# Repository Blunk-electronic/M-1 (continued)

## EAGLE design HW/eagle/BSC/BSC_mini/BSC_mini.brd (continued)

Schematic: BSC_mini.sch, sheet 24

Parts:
D2401, D2402, D2403: 1N4148; S_SOD123
LED2401: blue; S_0805; PART_CODE_BEL LED_PAC_S_0805_VAL_blue
LED2402, LED2404: green; S_0805; PART_CODE_BEL LED_PAC_S_0805_VAL_green
LED2403: yellow; S_0805; PART_CODE_BEL LED_PAC_S_0805_VAL_yellow
R2401, R2402, R2403, R2405, R2407: 2k7; S_0805; PART_CODE_BEL R_PAC_S_0805_VAL_2k7
R2404: 330; S_0805; PART_CODE_BEL R_PAC_S_0805_VAL_330
R2406, R2409: 160; S_0805; PART_CODE_BEL R_PAC_S_0805_VAL_160
R2408: 470; S_0805; PART_CODE_BEL R_PAC_S_0805_VAL_470
T2401, T2402, T2403, T2404, T2405, T2406: NX2301P; S_SOT23; PART_CODE_BEL T_PAC_S_SOT23_VAL_NX2301P
T2407, T2408: DMG3420U; S_SOT23; PART_CODE_BEL T_PAC_S_SOT23_VAL_DMG3420U

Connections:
GND: LED2401.C, LED2402.C, LED2404.C, R2401.2, R2402.2, R2403.2, R2405.2, T2407.2 (S), T2408.2 (S); also elsewhere on the board
MON_SP_1_VCC_P1V5_LED_A: LED2401.A, R2404.1
MON_SP_1_VCC_P1V8_LED_A: LED2402.A, R2406.2
MON_SP_1_VCC_P2V5_LED_A: LED2404.A, R2409.2
MON_SP_1_VCC_P3V3_D: R2407.2, T2407.3 (D), T2408.1 (G)
MON_SP_1_VCC_P3V3_G: D2401.C, D2402.C, D2403.C, R2405.1, T2407.1 (G)
MON_SP_1_VCC_P3V3_LED_A: LED2403.A, R2408.2
MON_SP_1_VCC_P3V3_LED_C: LED2403.C, T2408.3 (D)
P3V3: R2407.1, R2408.1, T2401.2 (S), T2402.2 (S), T2403.2 (S), T2404.2 (S), T2405.2 (S), T2406.2 (S); also elsewhere on the board
SP_1_VCC_P1V5_SET: T2401.1 (G); also elsewhere on the board
SP_1_VCC_P1V5_SET_N: R2401.1, T2401.3 (D), T2404.1 (G)
SP_1_VCC_P1V5_SET_OR: D2403.A, R2404.2, T2404.3 (D)
SP_1_VCC_P1V8_SET: T2402.1 (G); also elsewhere on the board
SP_1_VCC_P1V8_SET_N: R2402.1, T2402.3 (D), T2405.1 (G)
SP_1_VCC_P1V8_SET_OR: D2402.A, R2406.1, T2405.3 (D)
SP_1_VCC_P2V5_SET: T2403.1 (G); also elsewhere on the board
SP_1_VCC_P2V5_SET_N: R2403.1, T2403.3 (D), T2406.1 (G)
SP_1_VCC_P2V5_SET_OR: D2401.A, R2409.1, T2406.3 (D)

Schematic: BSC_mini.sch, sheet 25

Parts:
D2501, D2502, D2503: 1N4148; S_SOD123
LED2501: blue; S_0805; PART_CODE_BEL LED_PAC_S_0805_VAL_blue
LED2502, LED2503: green; S_0805; PART_CODE_BEL LED_PAC_S_0805_VAL_green
LED2504: yellow; S_0805; PART_CODE_BEL LED_PAC_S_0805_VAL_yellow
R2501, R2502, R2503, R2505, R2507: 2k7; S_0805; PART_CODE_BEL R_PAC_S_0805_VAL_2k7
R2504: 330; S_0805; PART_CODE_BEL R_PAC_S_0805_VAL_330
R2506, R2508: 160; S_0805; PART_CODE_BEL R_PAC_S_0805_VAL_160
R2509: 470; S_0805; PART_CODE_BEL R_PAC_S_0805_VAL_470
T2501, T2502, T2503, T2504, T2505, T2506: NX2301P; S_SOT23; PART_CODE_BEL T_PAC_S_SOT23_VAL_NX2301P
T2507, T2508: DMG3420U; S_SOT23; PART_CODE_BEL T_PAC_S_SOT23_VAL_DMG3420U

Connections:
GND: LED2501.C, LED2502.C, LED2503.C, R2501.2, R2502.2, R2503.2, R2505.2, T2507.2 (S), T2508.2 (S); also elsewhere on the board
MON_SP_2_VCC_P1V5_LED_A: LED2501.A, R2504.1
MON_SP_2_VCC_P1V8_LED_A: LED2502.A, R2506.2
MON_SP_2_VCC_P2V5_LED_A: LED2503.A, R2508.2
MON_SP_2_VCC_P3V3_D: R2507.2, T2507.3 (D), T2508.1 (G)
MON_SP_2_VCC_P3V3_G: D2501.C, D2502.C, D2503.C, R2505.1, T2507.1 (G)
MON_SP_2_VCC_P3V3_LED_A: LED2504.A, R2509.2
MON_SP_2_VCC_P3V3_LED_C: LED2504.C, T2508.3 (D)
P3V3: R2507.1, R2509.1, T2501.2 (S), T2502.2 (S), T2503.2 (S), T2504.2 (S), T2505.2 (S), T2506.2 (S); also elsewhere on the board
SP_2_VCC_P1V5_SET: T2501.1 (G); also elsewhere on the board
SP_2_VCC_P1V5_SET_N: R2501.1, T2501.3 (D), T2504.1 (G)
SP_2_VCC_P1V5_SET_OR: D2503.A, R2504.2, T2504.3 (D)
SP_2_VCC_P1V8_SET: T2502.1 (G); also elsewhere on the board
SP_2_VCC_P1V8_SET_N: R2502.1, T2502.3 (D), T2505.1 (G)
SP_2_VCC_P1V8_SET_OR: D2502.A, R2506.1, T2505.3 (D)
SP_2_VCC_P2V5_SET: T2503.1 (G); also elsewhere on the board
SP_2_VCC_P2V5_SET_N: R2503.1, T2503.3 (D), T2506.1 (G)
SP_2_VCC_P2V5_SET_OR: D2501.A, R2508.1, T2506.3 (D)

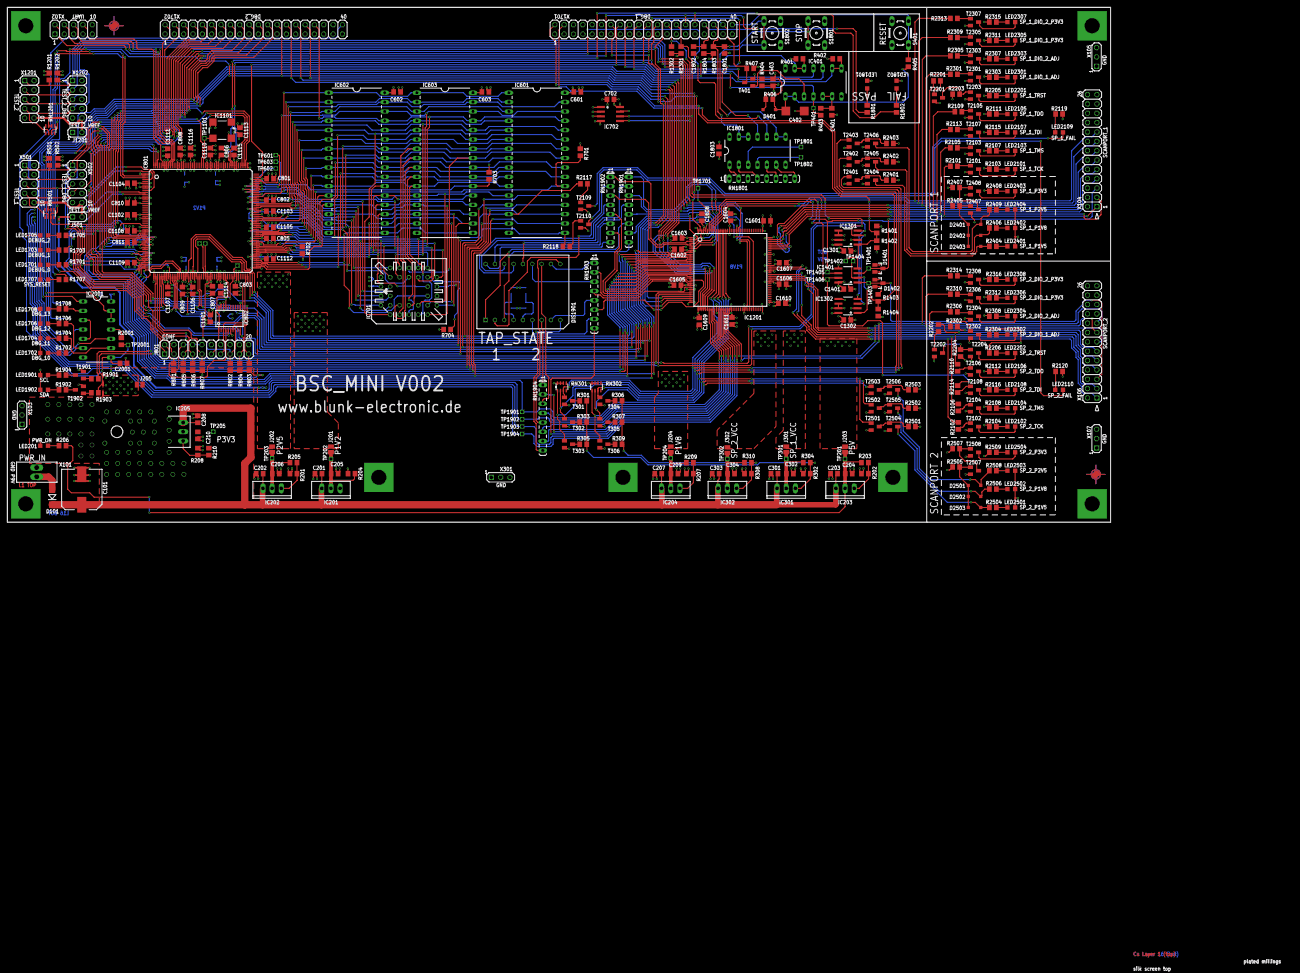
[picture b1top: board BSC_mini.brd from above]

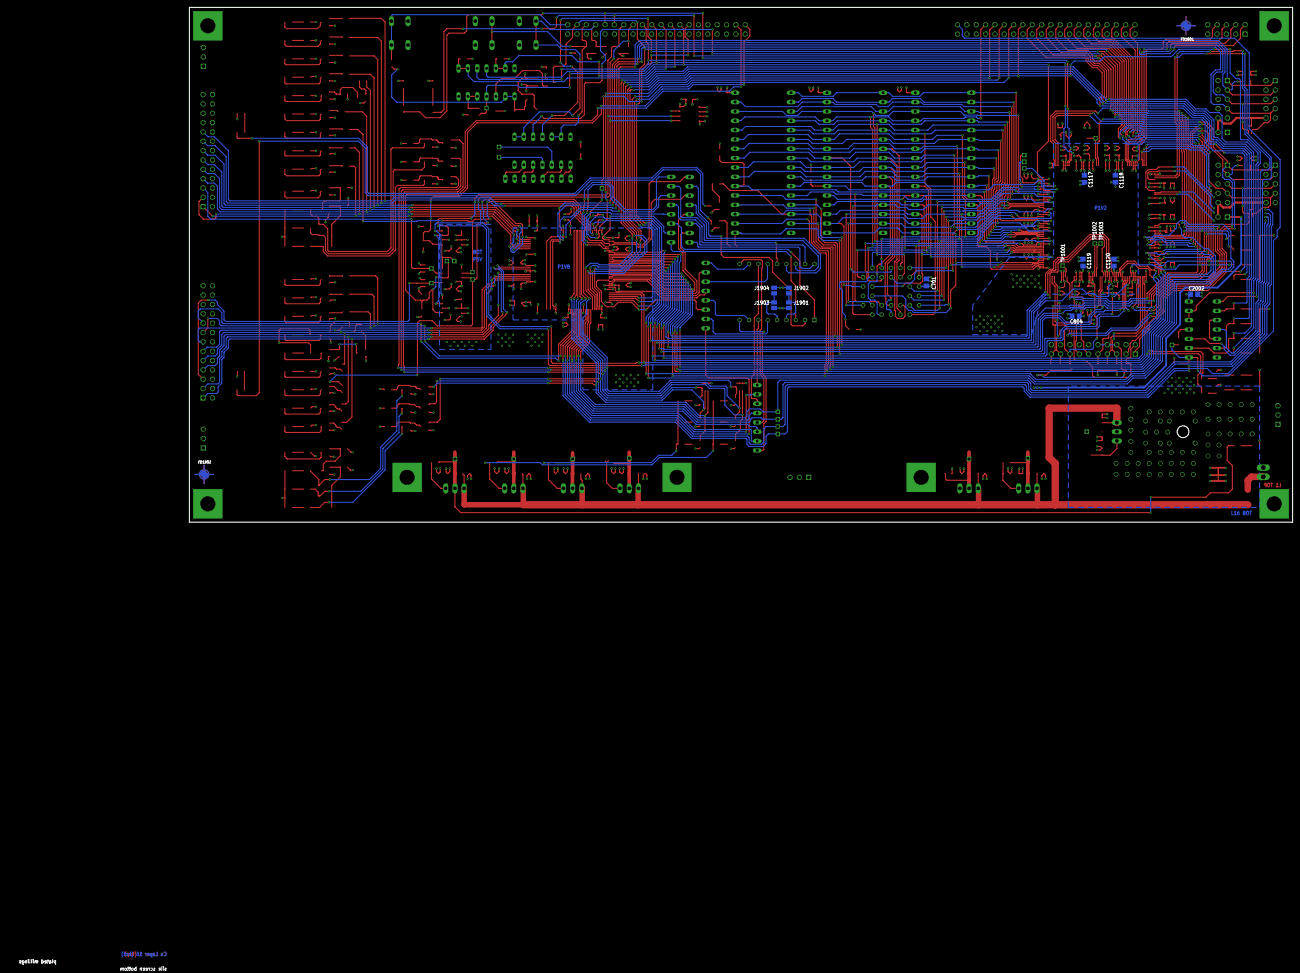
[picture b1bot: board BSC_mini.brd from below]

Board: 4 copper layers, 349.5 x 260.5 mm, 398 parts (14 on the bottom side), 329 nets.

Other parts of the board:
U$40: A3_LANDSCAPE

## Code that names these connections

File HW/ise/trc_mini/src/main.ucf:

# Target: XC2C384 in TQ144 package

# I2C MAIN BUS
NET "SCL"					LOC =  "P32";
NET "SDA"					LOC =  "P31";

# ON BOARD INTERCONNECTS
#NET "OBI_1" 				LOC = "P139";
#NET "OBI_2"				LOC =  "P52";
#NET "OBI_3"				LOC =  "P51";
#NET "OBI_4" 				LOC =  "P45";
#NET "OBI_5" 				LOC =  "P43";


# 7 SEGMENT DISPLAYS
NET "SEG_OUT_1[0]"			LOC = "P7"; # A
NET "SEG_OUT_1[1]"			LOC = "P6"; # B
NET "SEG_OUT_1[2]"			LOC = "P4"; # C
NET "SEG_OUT_1[3]"			LOC = "P2"; # D
NET "SEG_OUT_1[4]"			LOC = "P3"; # E
NET "SEG_OUT_1[5]"			LOC = "P5"; # F
NET "SEG_OUT_1[6]"			LOC = "P23"; # G
NET "SEG_OUT_1[7]"			LOC = "P25"; # H

NET "SEG_OUT_2[0]"			LOC = "P26"; # A
NET "SEG_OUT_2[1]"			LOC = "P28"; # B
NET "SEG_OUT_2[2]"			LOC = "P24"; # C
NET "SEG_OUT_2[3]"			LOC = "P50"; # D
NET "SEG_OUT_2[4]"			LOC = "P49"; # E
NET "SEG_OUT_2[5]"			LOC = "P44"; # F
NET "SEG_OUT_2[6]"			LOC = "P46"; # G
NET "SEG_OUT_2[7]"			LOC = "P48"; # H


# SCANPORTS
NET "SP_1_TRST_N" 			LOC = "P106";
NET "SP_2_TRST_N" 			LOC =  "P86";
NET "SP_1_TCK"				LOC = "P104";
NET "SP_2_TCK"				LOC =  "P92";
NET "SP_1_TMS"				LOC = "P103";
NET "SP_2_TMS"				LOC =  "P91";
NET "SP_1_TDO"				LOC = "P107";
NET "SP_2_TDO"				LOC =  "P88";

# DIO ADJUSTABLE # currently not used
#NET "SP_1_DIO_1_ADJ"		LOC = "P102";
#NET "SP_1_DIO_2_ADJ"		LOC = "P105";
#NET "SP_2_DIO_1_ADJ"		LOC =  "P87";
#NET "SP_2_DIO_2_ADJ"		LOC =  "P85";

# DIO P3V3 # currently not used
#NET "SP_1_DIO_1_P3V3"		LOC = "P135";
#NET "SP_1_DIO_2_P3V3"		LOC = "P136";
#NET "SP_2_DIO_1_P3V3"		LOC =  "P53";
#NET "SP_2_DIO_2_P3V3"		LOC =  "P54";


# COMPARATOR OUTPUTS
NET "SP_1_TDI_COMP" 		LOC = "P137";
NET "SP_2_TDI_COMP" 		LOC = "P138";

# RESET
NET "SYS_RESET" 			LOC = "P35";

# SCANPORT FPGA-CPLD
NET "SP_1_TCK_FPGA" 		LOC = "P9";
NET "SP_1_TDI_FPGA" 		LOC = "P17";
NET "SP_1_TMS_FPGA" 		LOC = "P10";
NET "SP_1_TDO_FPGA" 		LOC = "P11";
NET "SP_1_TRST_FPGA" 		LOC = "P12";

NET "SP_2_TCK_FPGA" 		LOC = "P13";
NET "SP_2_TDI_FPGA" 		LOC = "P18";
NET "SP_2_TMS_FPGA" 		LOC = "P14";
NET "SP_2_TDO_FPGA" 		LOC = "P15";
NET "SP_2_TRST_FPGA" 		LOC = "P16";


# SCANPORT VCCIO ADJUSTMENT
NET "SP_1_VCC_P1V5_SET" 	LOC = "P134";
NET "SP_1_VCC_P1V8_SET" 	LOC = "P133";
NET "SP_1_VCC_P2V5_SET" 	LOC = "P132";

NET "SP_2_VCC_P1V5_SET" 	LOC = "P131";
NET "SP_2_VCC_P1V8_SET" 	LOC = "P130";
NET "SP_2_VCC_P2V5_SET" 	LOC = "P129";

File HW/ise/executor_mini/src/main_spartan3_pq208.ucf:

# MEMORY (RAM / FLASH EEPROM)
NET "MEM_D<0>" 			LOC = P106 | IOSTANDARD = LVTTL;
NET "MEM_D<1>" 			LOC = P107 | IOSTANDARD = LVTTL;
NET "MEM_D<2>" 			LOC = P108 | IOSTANDARD = LVTTL;
NET "MEM_D<3>" 			LOC = P109 | IOSTANDARD = LVTTL;
NET "MEM_D<4>" 			LOC = P111 | IOSTANDARD = LVTTL;
NET "MEM_D<5>" 			LOC = P113 | IOSTANDARD = LVTTL;
NET "MEM_D<6>" 			LOC = P114 | IOSTANDARD = LVTTL;
NET "MEM_D<7>"			LOC = P115 | IOSTANDARD = LVTTL;

NET "MEM_A<0>" 			LOC = P122 | IOSTANDARD = LVTTL;
NET "MEM_A<1>" 			LOC = P123 | IOSTANDARD = LVTTL;
NET "MEM_A<2>" 			LOC = P124 | IOSTANDARD = LVTTL;
NET "MEM_A<3>" 			LOC = P125 | IOSTANDARD = LVTTL;
NET "MEM_A<4>" 			LOC = P126 | IOSTANDARD = LVTTL;
NET "MEM_A<5>" 			LOC = P128 | IOSTANDARD = LVTTL;
NET "MEM_A<6>" 			LOC = P130 | IOSTANDARD = LVTTL;
NET "MEM_A<7>" 			LOC = P131 | IOSTANDARD = LVTTL;
NET "MEM_A<8>" 			LOC = P132 | IOSTANDARD = LVTTL;
NET "MEM_A<9>" 			LOC = P133 | IOSTANDARD = LVTTL;
NET "MEM_A<10>" 		LOC = P135 | IOSTANDARD = LVTTL;
NET "MEM_A<11>" 		LOC = P137 | IOSTANDARD = LVTTL;
NET "MEM_A<12>" 		LOC = P138 | IOSTANDARD = LVTTL;
NET "MEM_A<13>" 		LOC = P139 | IOSTANDARD = LVTTL;
NET "MEM_A<14>" 		LOC = P140 | IOSTANDARD = LVTTL;
NET "MEM_A<15>" 		LOC = P141 | IOSTANDARD = LVTTL;
NET "MEM_A<16>" 		LOC = P143 | IOSTANDARD = LVTTL;
NET "MEM_A<17>" 		LOC = P144 | IOSTANDARD = LVTTL;
NET "MEM_A<18>" 		LOC = P146 | IOSTANDARD = LVTTL;

NET "RAM_OUT_CS_1_N" 	LOC = P116 | IOSTANDARD = LVTTL;
NET "RAM_OUT_CS_2_N" 	LOC = P147 | IOSTANDARD = LVTTL;
NET "RAM_IN_CS_N" 		LOC = P117 | IOSTANDARD = LVTTL;
NET "ROM_CS_N" 			LOC = P148 | IOSTANDARD = LVTTL;
NET "MEM_OE_N" 			LOC = P120 | IOSTANDARD = LVTTL;
NET "MEM_WE_N" 			LOC = P119 | IOSTANDARD = LVTTL;


# RESET
NET "SYS_RESET_N" 		LOC = P182 | IOSTANDARD = LVTTL;

# UART
NET "UART_RTS" 			LOC = P198 | IOSTANDARD = LVTTL;
NET "UART_CTS" 			LOC = P199 | IOSTANDARD = LVTTL;
NET "UART_TXD" 			LOC = P200 | IOSTANDARD = LVTTL;
NET "UART_RXD" 			LOC = P203 | IOSTANDARD = LVTTL;

# CLOCK
NET "CLK_MASTER" 		LOC = P181 | IOSTANDARD = LVTTL;
NET "CLK_SLOW"			LOC = P154 | IOSTANDARD = LVTTL;

# SCHMITT-TRIGGERS
NET "ST_1_OUT"			LOC = P166 | IOSTANDARD = LVTTL;
NET "ST_2_OUT"			LOC = P165 | IOSTANDARD = LVTTL;

# DIGITAL CLUSTER
NET "DCL_OUT"			LOC = P3 | IOSTANDARD = LVTTL;
NET "ACL_OUT"			LOC = P2 | IOSTANDARD = LVTTL;

# SCANPORT FPGA-CPLD
NET "SP_1_TCK_FPGA"		LOC = P76 | IOSTANDARD = LVTTL;
NET "SP_2_TCK_FPGA"		LOC = P77 | IOSTANDARD = LVTTL;
NET "SP_1_TMS_FPGA"		LOC = P74 | IOSTANDARD = LVTTL;
NET "SP_2_TMS_FPGA"		LOC = P72 | IOSTANDARD = LVTTL;
NET "SP_1_TDO_FPGA"		LOC = P68 | IOSTANDARD = LVTTL;
NET "SP_2_TDO_FPGA"		LOC = P67 | IOSTANDARD = LVTTL;
NET "SP_1_TRST_FPGA"	LOC = P65 | IOSTANDARD = LVTTL;
NET "SP_2_TRST_FPGA"	LOC = P64 | IOSTANDARD = LVTTL;
NET "SP_1_FAIL_FPGA"	LOC = P63 | IOSTANDARD = LVTTL;
NET "SP_2_FAIL_FPGA"	LOC = P62 | IOSTANDARD = LVTTL;
NET "SP_1_TDI_FPGA"		LOC = P78 | IOSTANDARD = LVTTL;
NET "SP_2_TDI_FPGA"		LOC = P71 | IOSTANDARD = LVTTL;


# DEBUG
NET "DEBUG<0>" 			LOC = P61 | IOSTANDARD = LVTTL; #low active, led green
NET "DEBUG<1>" 			LOC = P33 | IOSTANDARD = LVTTL; #low active, led yellow
NET "DEBUG<2>" 			LOC = P44 | IOSTANDARD = LVTTL; #low active, led blue


# PUSH BUTTONS AND STATUS LEDS
NET "CTRL_IN_START_N"	LOC = P35 | IOSTANDARD = LVTTL;
NET "CTRL_IN_STOP_N" 	LOC = P34 | IOSTANDARD = LVTTL;
NET "CTRL_OUT_PASS" 	LOC = P57 | IOSTANDARD = LVTTL;
NET "CTRL_OUT_FAIL" 	LOC = P58 | IOSTANDARD = LVTTL;
	

#I2C
NET "I2C_SDA" 			LOC = P52 | IOSTANDARD = LVTTL;
NET "I2C_SCL" 			LOC = P51 | IOSTANDARD = LVTTL;

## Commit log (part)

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2016-09-23 added dummy uut mmu
2016-09-23 installing doc files disabled
2016-09-23 updated model
2016-09-23 added a readme.txt in tmp dir
2016-09-23 added bak directory
2016-09-23 build scripts create tmp and bak dir
2016-09-23 added uninstaller
2016-09-23 updated Un/installer
2016-09-23 bugfixes
2016-09-23 started gui
2016-09-27 cleaned up
2016-09-29 procedure check_environment moved to m1_internal.adb
2016-09-29 gui launches scripts, and tests
2016-09-29 backup
2016-09-29 moved gui to bsmgui
2016-09-29 button abort
2016-09-29 gui acceptable
2016-09-30 experimented with spawn
2016-10-01 cancel test
2016-10-03 test start and abort ok
2016-10-04 script launch and abort works
2016-10-04 added gnatclean
2016-10-04 added filter for scripts
2016-10-04 updated manual with script extensions
2016-10-04 notes about things to do
2016-10-04 fixed button labels
2016-10-04 added screenshots
2016-10-05 - reordered buttons - update manual - messages from pidof diverted to trash bin
2016-10-05 bugfix
2016-10-06 added script-end-mark
2016-10-07 improved stop/abort functions
2016-10-07 bsc ram cleared on uut change
2016-10-07 reading session.conf
2016-10-07 described screenshots in production mode
2016-10-10 session configuration finished
2016-10-10 bufix
2016-10-12 made notes and comments
2016-10-12 initiated german manual
2016-10-18 added todo notes
2016-10-20 upated manuals
2016-10-22 updated manuals
2016-10-24 update manual
2016-10-25 removed odt docs
2016-10-26 scanport output voltage is now checked if itis supported by bsc
2016-10-26 reading database now checks valid discrete scanport output voltage
2016-11-01 started rework
2016-11-03 started reading boundary register
2016-11-03 reads cell id
2016-11-03 read boundary register
2016-11-03 - cleaned up - comments on reading the boundary register cells - added program position value
2016-11-04 safevalues write
2016-11-04 read safebits complete
2016-11-04 read opcodes under construction
2016-11-05 read instruction name
2016-11-07 instruction opcodes reading ok
2016-11-07 subsection boundary_register under contstruction
2016-11-07 subsection instruction_opcode writing complete
2016-11-08 port io map
2016-11-08 port pin map under construction
2016-11-09 port pin map complete
2016-11-09 added exception handler
2016-11-09 bugfix: procedure trim_port_pin_map variable port is now an extended_string
2016-11-09 bugfix: preliminary data base used for initial reading
2016-11-09 option remove prefix under construction
2016-11-10 option remove pin prefix
2016-11-10 moved functions and procedures to m1_internal
2016-11-11 started with net container
2016-11-11 bugfix when calling procedure extract_section
2016-11-11 started writing cell id
2016-11-12 writing cell info complete
2016-11-14 fixed base address calculation for scanparth 2
2016-11-17 check for one-pin nets
2016-11-18 fixed make process
2016-12-01 ram clear reworked
2016-12-01 reworked ram dump
2016-12-02 reworked status query
2016-12-02 reworked upload
2016-12-05 reworked shutdown
2016-12-06 reworked set breakpoint
2016-12-06 added -gnat2012 option and sercom packages in makefiles
2016-12-06 removed kermit stuff
2016-12-06 removed train-z stuff
2016-12-06 removed dir CAD and HDL
2016-12-06 added -gnat2012 option
2016-12-08 added make process for gui
2016-12-08 checks if BSC is connected
2016-12-09 switched serial communication back to recompiled g-sercom RTL
2017-03-02 fixed installer
2017-03-02 indefiniete container for bics
2017-03-03 rework
2017-03-04 started rework mkoptions. started protel importer
2017-03-06 assembly variants
2017-03-07 apply assembly variants on device list
2017-03-07 apply assembly variants on nets started
2017-03-07 function pin_occurence_in_net
2017-03-08 write skeleton started
2017-03-08 adopted bsmcl to impprotel
2017-03-08 removed new_line on one-pin warning
2017-03-08 bsmcl passes target module and prefix to impprotel
2017-03-09 read mkoptions.conf section connectors
2017-03-09 moved functions and procedures database related to m1_database
2017-03-13 type change of database file name
2017-03-14 added pin counter
2017-03-23 added more details
2017-03-27 added m1_test_gen_and_exec.o
2017-03-29 rework on database stuff done
2017-03-30 fixed link to include directory
2017-03-30 database integrity check
2017-03-31 rework bsmcl done
2017-03-31 reworked cell list dumping
2017-04-03 started rework update cell lists
2017-04-04 fixed makefile
2017-04-04 added prog_position
2017-04-05 rework done
2017-04-05 read options
2017-04-06 made version a constant
2017-04-07 lots of bugfixes
2017-04-07 started writing logfile
2017-04-10 bugfix and improved log
2017-04-11 improved exception handlers
2017-04-11 cleaned up global variables. moved them where they belong
2017-04-11 creates and writes logfile
2017-04-11 started function that detects wildcards in bridge name
2017-04-12 reading bridges and connector pairs complete
2017-04-12 started make_netlist
2017-04-13 procedure find_device_by_net
2017-04-13 Prespecification for find_net_by_device_and_pin
2017-04-18 warning on missing bridge device
2017-04-18 bridge_valid flag
2017-04-19 started function wildcard_matches
2017-04-19 commented
2017-04-20 function bridge_is_listed
2017-04-20 bugfix in procedure add_bridges_matching_wildcard_to_list_of_bridges
2017-04-21 procedure verify_array_pins checks occurences of pins
2017-04-21 improved log messages when transit to net
2017-04-24 rework procedures find_pin and find_net
2017-04-24 started sorting clusters
2017-04-25 commented, removed m1.o from makefile
2017-04-25 started sorting bs clusters
2017-04-25 started procedure write_non_bs_clusters
2017-04-25 modified for testing purposes
2017-04-26 updated and put more comments in it
2017-04-26 statistics are now written in options file
2017-04-26 write routing information in csv file
2017-04-27 added discriminant is_bs_capable to type_pin
2017-04-27 type_pin equippend with a discriminant bs_capable
2017-04-27 cell info is now written in options file
2017-04-27 adopted new package names. changed default device class assignment
2017-04-27 added impprotel to installer script
2017-04-27 changed default device class from ? to NA
2017-04-28 updated install tools
2017-04-28 connector pin range type added
2017-04-28 improved netlist importer
2017-04-28 added arguments for target level and prefix
2017-04-28 bugfix and installer updated
2017-04-29 added log messages
2017-05-01 improved log messages
2017-05-01 bugfix: when no assembly variants used, all devices and pins are to be mounted
2017-05-01 removed unneccesary package prefixes
2017-05-04 cleaned up, commented a lot
2017-05-04 moved former global variables to functions and procedures where they belog
2017-05-04 cleaned up, commented things to do
2017-05-04 bugfix on writing default device class
2017-05-05 variable skeleton added
2017-05-05 the prefix is applied when writing the skeleton
2017-05-05 rework done, testing required
2017-05-05 updated installers
2017-05-05 bugfix on applying prefix
2017-05-05 bugfix when writing statistics
2017-05-08 left a not about things to do
2017-05-08 advise to use dos2unix
2017-05-08 improved log messages and bugfix
2017-05-08 stale skeletons are deleted if new variants list has been created
2017-05-08 pin range under construction
2017-05-08 pin range support
2017-05-09 fixed additional information in net header
2017-05-09 writes pin legend
2017-05-09 bugfix on class NA request
2017-05-10 reworked log messages
2017-05-13 removed old m1 stuff
2017-05-16 notes on things to do
2017-05-17 formatted exeption handler
2017-05-17 updated makefile
2017-05-18 rework finished
2017-05-18 updated installer
2017-05-19 bugfix: input cell if bidir pins not written anymore
2017-05-19 commented non-optimized nets
2017-05-19 started rework mktoggle
2017-05-20 reworked log messages at main level
2017-05-23 started rework log messages
2017-05-24 started rework procedure compile_command
2017-05-26 bugfix on computing scanpath base address
2017-05-29 reduced integity check level to light
2017-05-29 testing
2017-06-01 bugfix, reset version number
2017-06-01 started changing list_of_bics to a map
2017-06-01 added link to repo
2017-06-02 continues changing list_of_bics to a map
2017-06-02 bics are now stored in a map
2017-06-03 while concatenating sxr images, the position of the bic is taken from selector position
2017-06-05 bisc are now stored in a map
2017-06-06 nets are stored in a map. started rework
2017-06-06 nets are stored in a map. rework finished
2017-06-07 nets are now stored in a map
2017-06-08 updated demo uut
2017-06-09 reworked gui
2017-06-09 moved libraries from external repository lbr_ada here
2017-06-12 bugfix in makefile
2017-06-13 started rework zuken netlist importer
2017-06-14 reading zuken netlist in vector list ok
2017-06-14 prepared writing skeleton
2017-06-15 procedure sort_netlist
2017-06-15 added a map of devices
2017-06-15 started rework write_skeleton
2017-06-15 prepared procedure write_regular_nets
2017-06-15 prepared change of list_of_nets to a map
2017-06-16 rework write_skeleton finished
2017-06-16 cleaned up. renamed types
2017-06-16 started testing zuken importer
2017-06-17 warning on no-name nets
2017-06-19 zuken importer creates viratual nets for unconnected pins
2017-06-19 bugfix, commented, cleaned up
2017-06-19 skips lines that contain things like fiducials
2017-06-20 fixed comments
2017-06-20 started kicad netlist importer
2017-06-20 started reading netlist
2017-06-21 work on procedure process_line
2017-06-23 added kicad test netlists
2017-06-26 started implemlenting algorithm on parsing kicad netlist
2017-06-26 commented things
2017-06-28 non-bracket enclosed argument is read properly
2017-06-28 procedure verify_cmd started
2017-06-29 testing sections
2017-06-30 development
2017-06-30 command is now a type_command instead of an unbounded string
2017-06-30 started evaluating commands
2017-06-30 first version seems to work, testing required
2017-06-30 updated make script
2017-06-30 added cad format kicad in case statements
2017-07-01 changed terminology from commmand to keyword or section name
2018-09-12 excluded gtkada for the time being
2018-09-15 status query shows address rf output
2018-09-15 ignore filter in mmu
2018-09-15 disabled EDAC
2018-09-17 - bug: compiler writes wrong number of test steps in vector file - fixed
2018-09-17 - removed reading RAM output data and displaying - why: on each read access to the data channel, the start address generated by rf increases. causes too much confusion to the operator
2018-09-17 enabled EDAC
2018-09-17 enabled 4 core compiling, disabled gui
2018-09-17 reordered things
2018-09-17 some test scripts
2018-09-18 debug serial if
2018-09-18 bugfix: generate ops require to mark active scanpaths
2018-09-18 comments on calculating driver voltages
2018-09-18 removed debug stuff
2018-09-18 fixed options files
2018-09-19 shorter row separator
2018-09-25 rework builder for gui
2018-09-25 rework install notes
2018-09-26 notes on installing gtkada
2018-09-26 note on machine arch
2018-10-04 - the order of bics in the register file header was wrong so far - they are now ordered by their pos. in scanpath starting with the lowest number
2018-10-11 The netlist should be closed properly and the standard input set. Placed this statements in comments. Testing required.
2018-10-11 fixed installers
2018-10-11 start imported for testexpert
2018-10-12 importer ready
2018-11-16 Make clean uses rm -f to not output error messages when target non-existent
2018-11-16 mkdir -p ~/bin in case it does not already exist
2018-11-16 gprclean in uninstaller
2019-05-31 move sw stuff into subdir
2019-05-31 opensource HW stuff
2019-07-03 track missing BST files
2019-07-03 fix impact configuration
2019-07-03 fix trc configuration
2019-08-08 add BSC photo
2019-08-08 rework headings
2019-08-08 why ada
2019-08-08 fix typing errors
2019-08-08 change header on ada
2019-08-10 change default directory for scripts
2019-08-15 voltages on testpoints
2019-08-16 load and run scripts
2019-08-21 notes on BST mode
2019-08-22 add photos
2019-08-22 more photos
2019-08-27 improve startup script
2019-09-13 improve script run-continuous so that failed tests are counted
2019-09-13 fix installer and uninstaller
2019-09-25 fix installer
2020-01-08 remove howto
